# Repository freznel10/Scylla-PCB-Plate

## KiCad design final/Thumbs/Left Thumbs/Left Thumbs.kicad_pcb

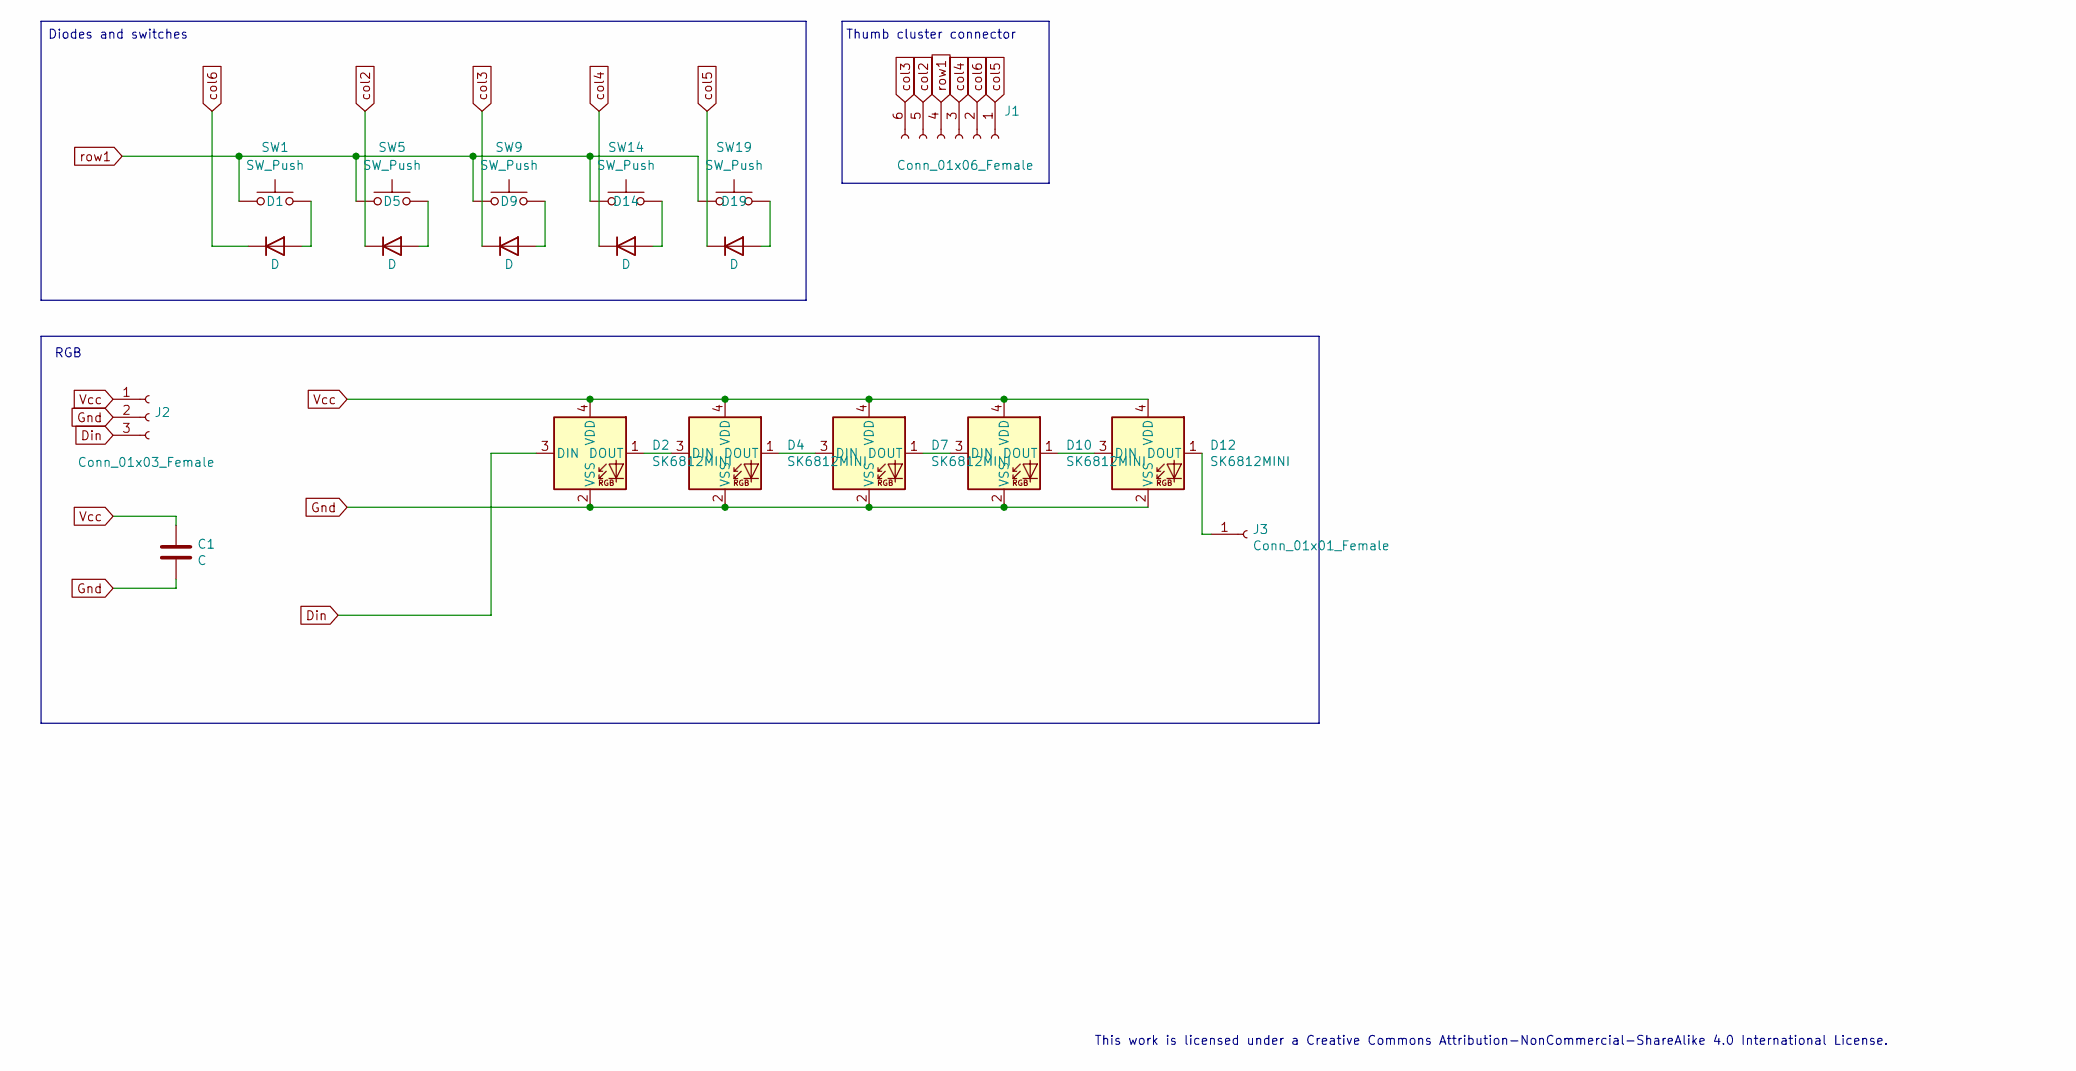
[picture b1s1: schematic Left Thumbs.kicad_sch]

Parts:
C1: C; C_0805_2012Metric_Pad1.18x1.45mm_HandSolder; LCSC C2798196
D1, D5, D9, D14, D19: D; Diode_TH_SOD123; LCSC C108804
D2, D4, D7, D10, D12: SK6812MINI; YS-SK6812MINI-E-bkb
J1: Conn_01x06_Female; PinHeader_1x06_P2.54mm_Vertical
J2: Conn_01x03_Female; PinHeader_1x03_P2.54mm_Vertical
J3: Conn_01x01_Female; PinHeader_1x01_P2.54mm_Vertical
SW1, SW5, SW9, SW14, SW19: SW_Push; SW_MX_KS_Choc-mod

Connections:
Din: D2.3 (DIN), J2.3
Gnd: C1.2, D2.2 (VSS), D4.2 (VSS), D7.2 (VSS), D10.2 (VSS), D12.2 (VSS), J2.2
unnamed: D1.2 (A), SW1.2
unnamed: D2.1 (DOUT), D4.3 (DIN)
unnamed: D4.1 (DOUT), D7.3 (DIN)
unnamed: D5.2 (A), SW5.2
unnamed: D9.2 (A), SW9.2
unnamed: D7.1 (DOUT), D10.3 (DIN)
unnamed: D10.1 (DOUT), D12.3 (DIN)
unnamed: D12.1 (DOUT), J3.1
unnamed: D14.2 (A), SW14.2
unnamed: D19.2 (A), SW19.2
Vcc: C1.1, D2.4 (VDD), D4.4 (VDD), D7.4 (VDD), D10.4 (VDD), D12.4 (VDD), J2.1
col2: D5.1 (K), J1.5
col3: D9.1 (K), J1.6
col4: D14.1 (K), J1.3
col5: D19.1 (K), J1.1
col6: D1.1 (K), J1.2
row1: J1.4, SW1.1, SW5.1, SW9.1, SW14.1, SW19.1

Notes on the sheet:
Diodes and switches
RGB
Thumb cluster connector
This work is licensed under a Creative Commons Attribution-NonCommercial-ShareAlike 4.0 International License.

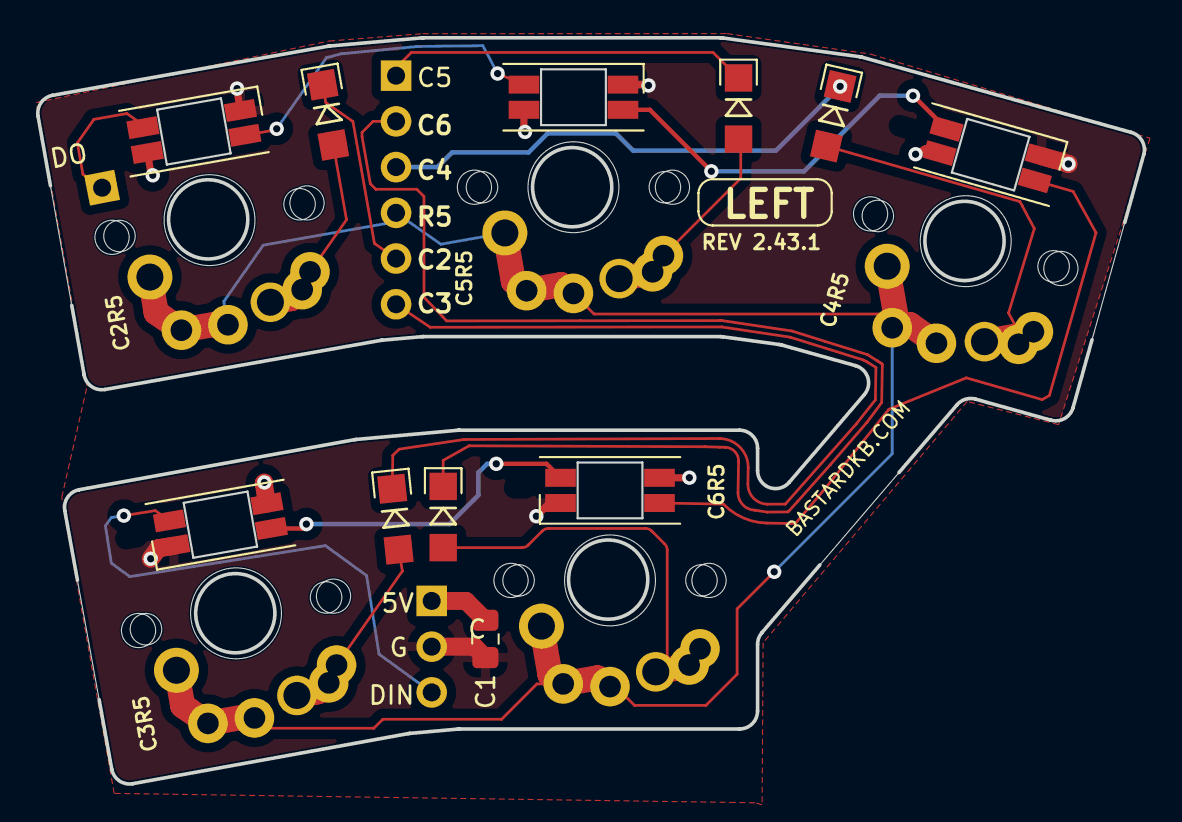
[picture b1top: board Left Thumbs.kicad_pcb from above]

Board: 4 copper layers, 61.5 x 41.5 mm, 19 parts (0 on the bottom side), 19 nets.

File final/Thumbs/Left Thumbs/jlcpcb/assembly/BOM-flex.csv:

Comment,Designator,Footprint,LCSC
D,"D1,D14,D19,D5,D9",Diode_TH_SOD123,C108804
C,C1,C_0805_2012Metric_Pad1.18x1.45mm_HandSolder,C2798196
Conn_01x03_Female,J2,PinHeader_1x03_P2.54mm_Vertical,
SK6812MINI,D4,YS-SK6812MINI-E-bkb,
SK6812MINI,D10,YS-SK6812MINI-E-bkb,
SW_Push,SW9,SW_MX_KS_Choc-mod,
SW_Push,SW19,SW_MX_KS_Choc-mod,
SW_Push,SW14,SW_MX_KS_Choc-mod,
SK6812MINI,D12,YS-SK6812MINI-E-bkb,
SK6812MINI,D2,YS-SK6812MINI-E-bkb,
Conn_01x06_Female,J1,PinHeader_1x06_P2.54mm_Vertical,
SW_Push,SW1,SW_MX_KS_Choc-mod,
SK6812MINI,D7,YS-SK6812MINI-E-bkb,
SW_Push,SW5,SW_MX_KS_Choc-mod,
Conn_01x01_Female,J3,PinHeader_1x01_P2.54mm_Vertical,

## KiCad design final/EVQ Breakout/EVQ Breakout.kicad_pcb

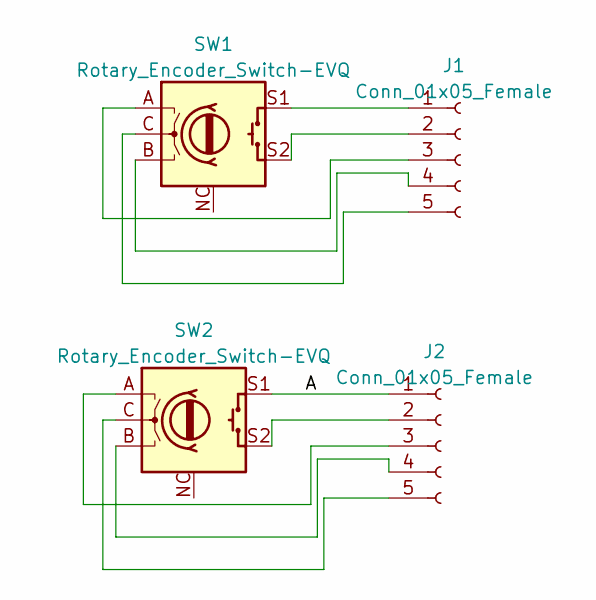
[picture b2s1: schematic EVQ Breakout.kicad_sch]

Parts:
J1, J2: Conn_01x05_Female; PinHeader_1x05_P2.00mm_Vertical
SW1, SW2: Rotary_Encoder_Switch-EVQ; EVQWGD001-sadek-no cutout

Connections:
unnamed: J1.1, SW1.S1
unnamed: J1.2, SW1.S2
unnamed: J1.3, SW1.A
unnamed: J1.4, SW1.B
unnamed: J1.5, SW1.C
unnamed: J2.1, SW2.S1
unnamed: J2.2, SW2.S2
unnamed: J2.3, SW2.A
unnamed: J2.4, SW2.B
unnamed: J2.5, SW2.C

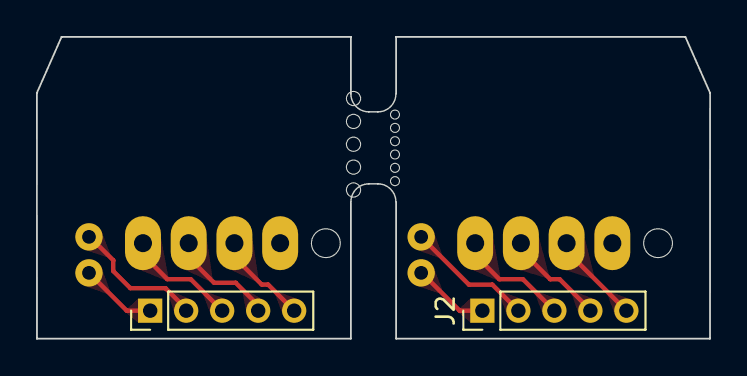
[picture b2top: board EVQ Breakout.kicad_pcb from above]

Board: 2 copper layers, 37.4 x 16.8 mm, 4 parts (0 on the bottom side), 10 nets.

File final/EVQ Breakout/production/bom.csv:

Designator,Footprint,Quantity,Value,LCSC Part #
"J1, J2",PinHeader_1x05_P2.00mm_Vertical,2,Conn_01x05_Female,
"SW1, SW2",EVQWGD001-sadek-no cutout,2,Rotary_Encoder_Switch-EVQ,

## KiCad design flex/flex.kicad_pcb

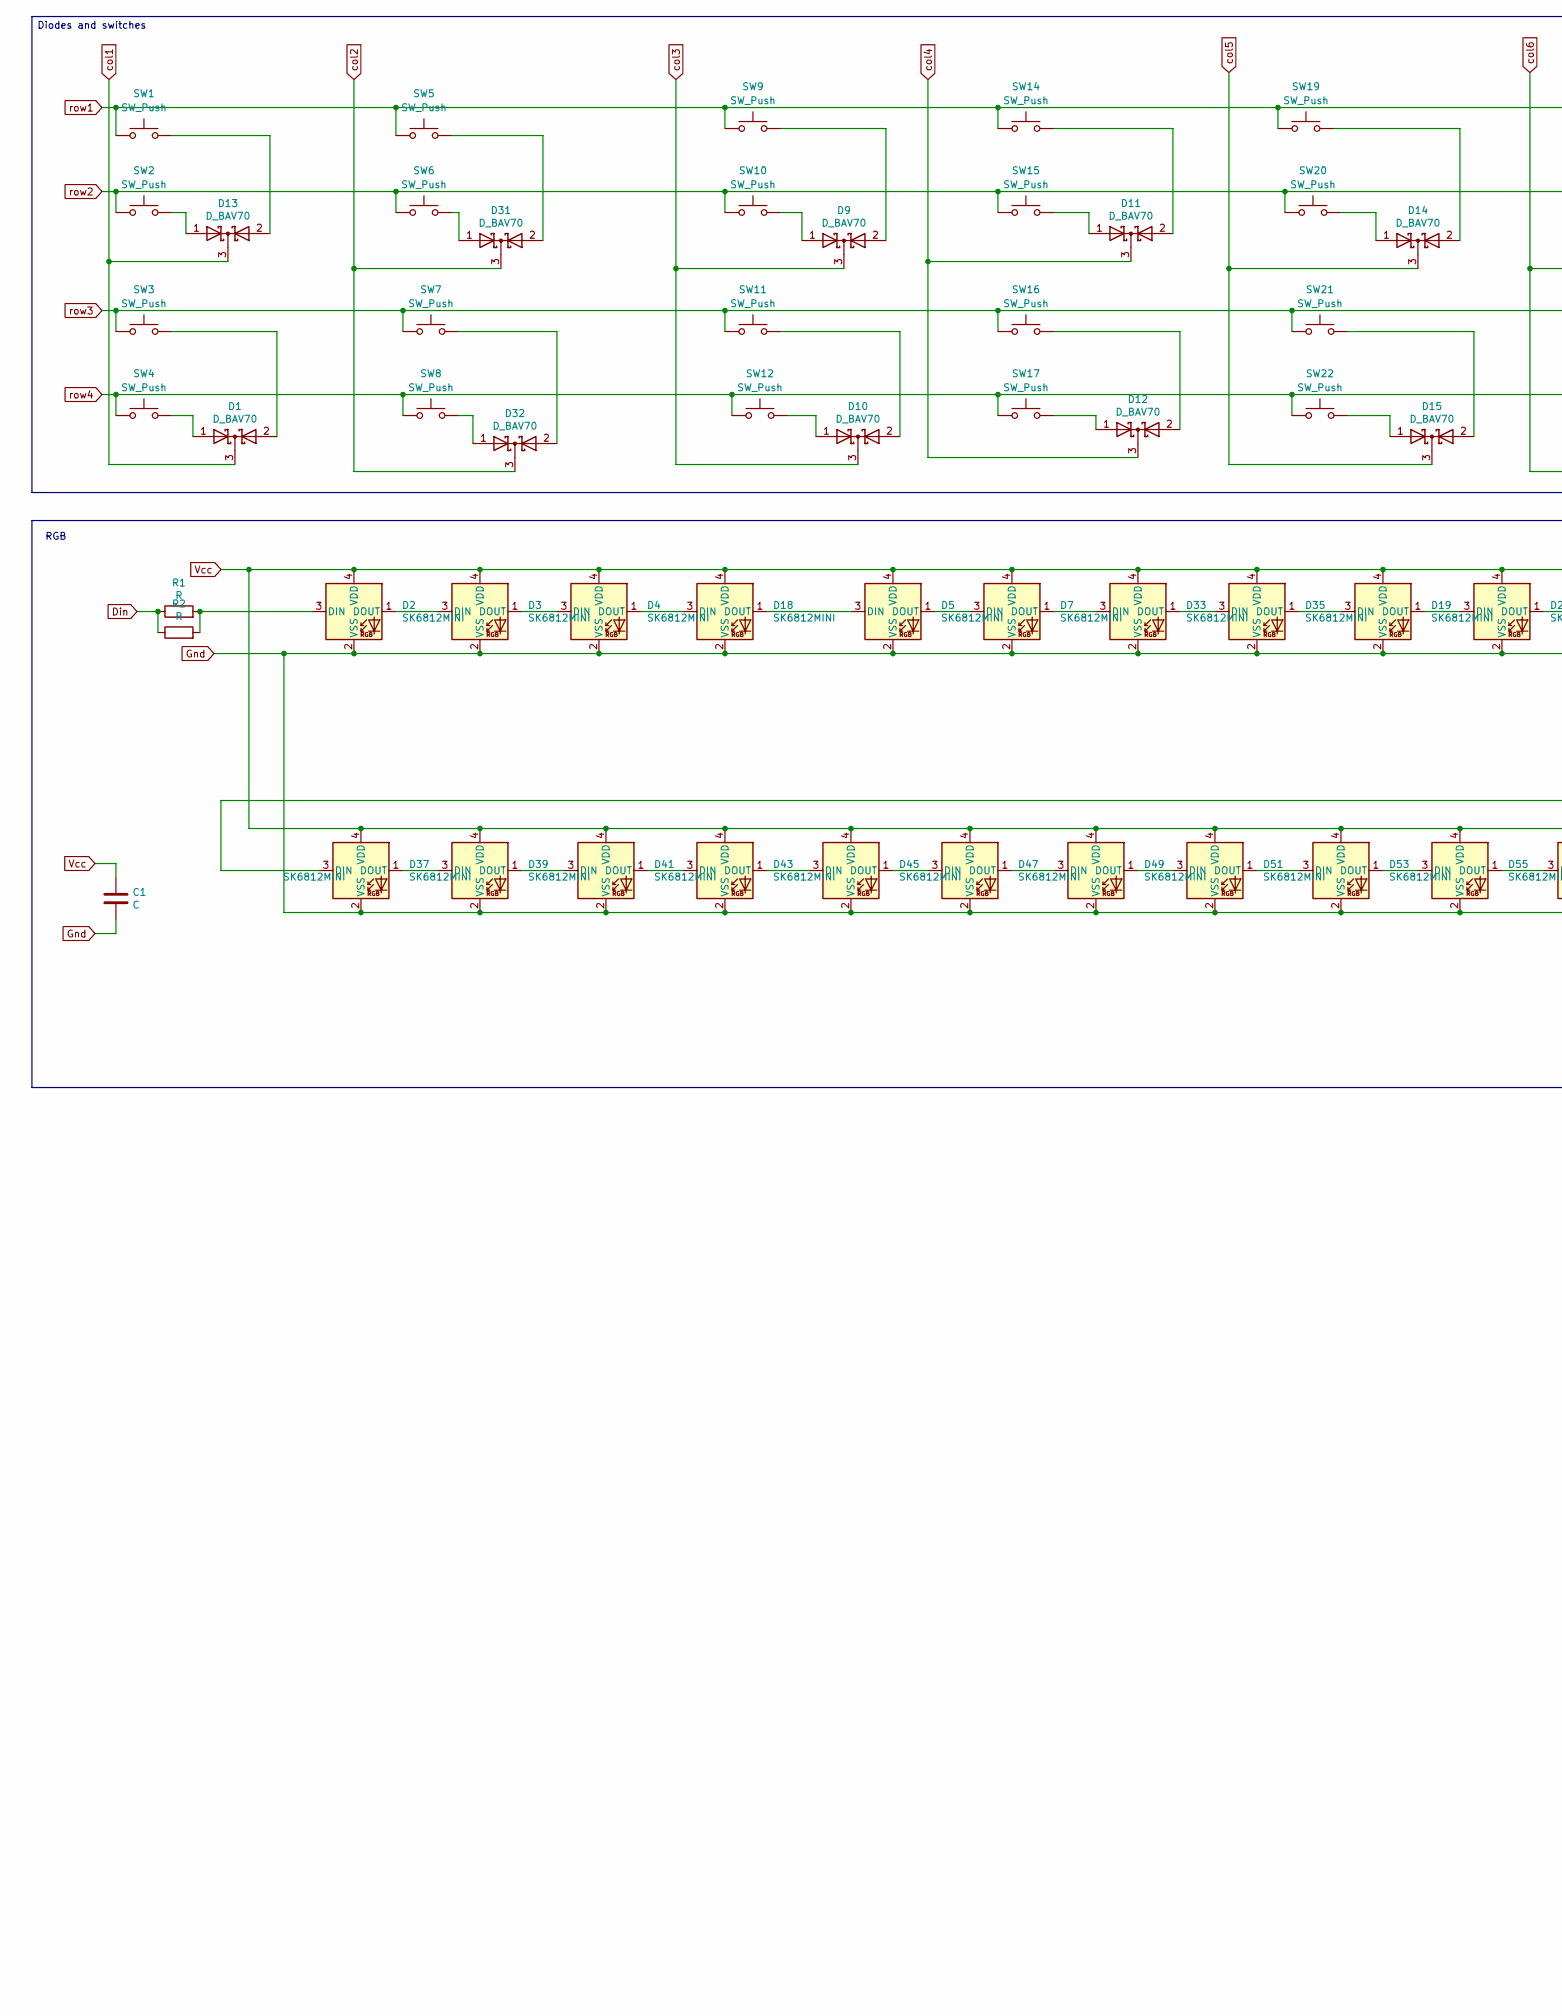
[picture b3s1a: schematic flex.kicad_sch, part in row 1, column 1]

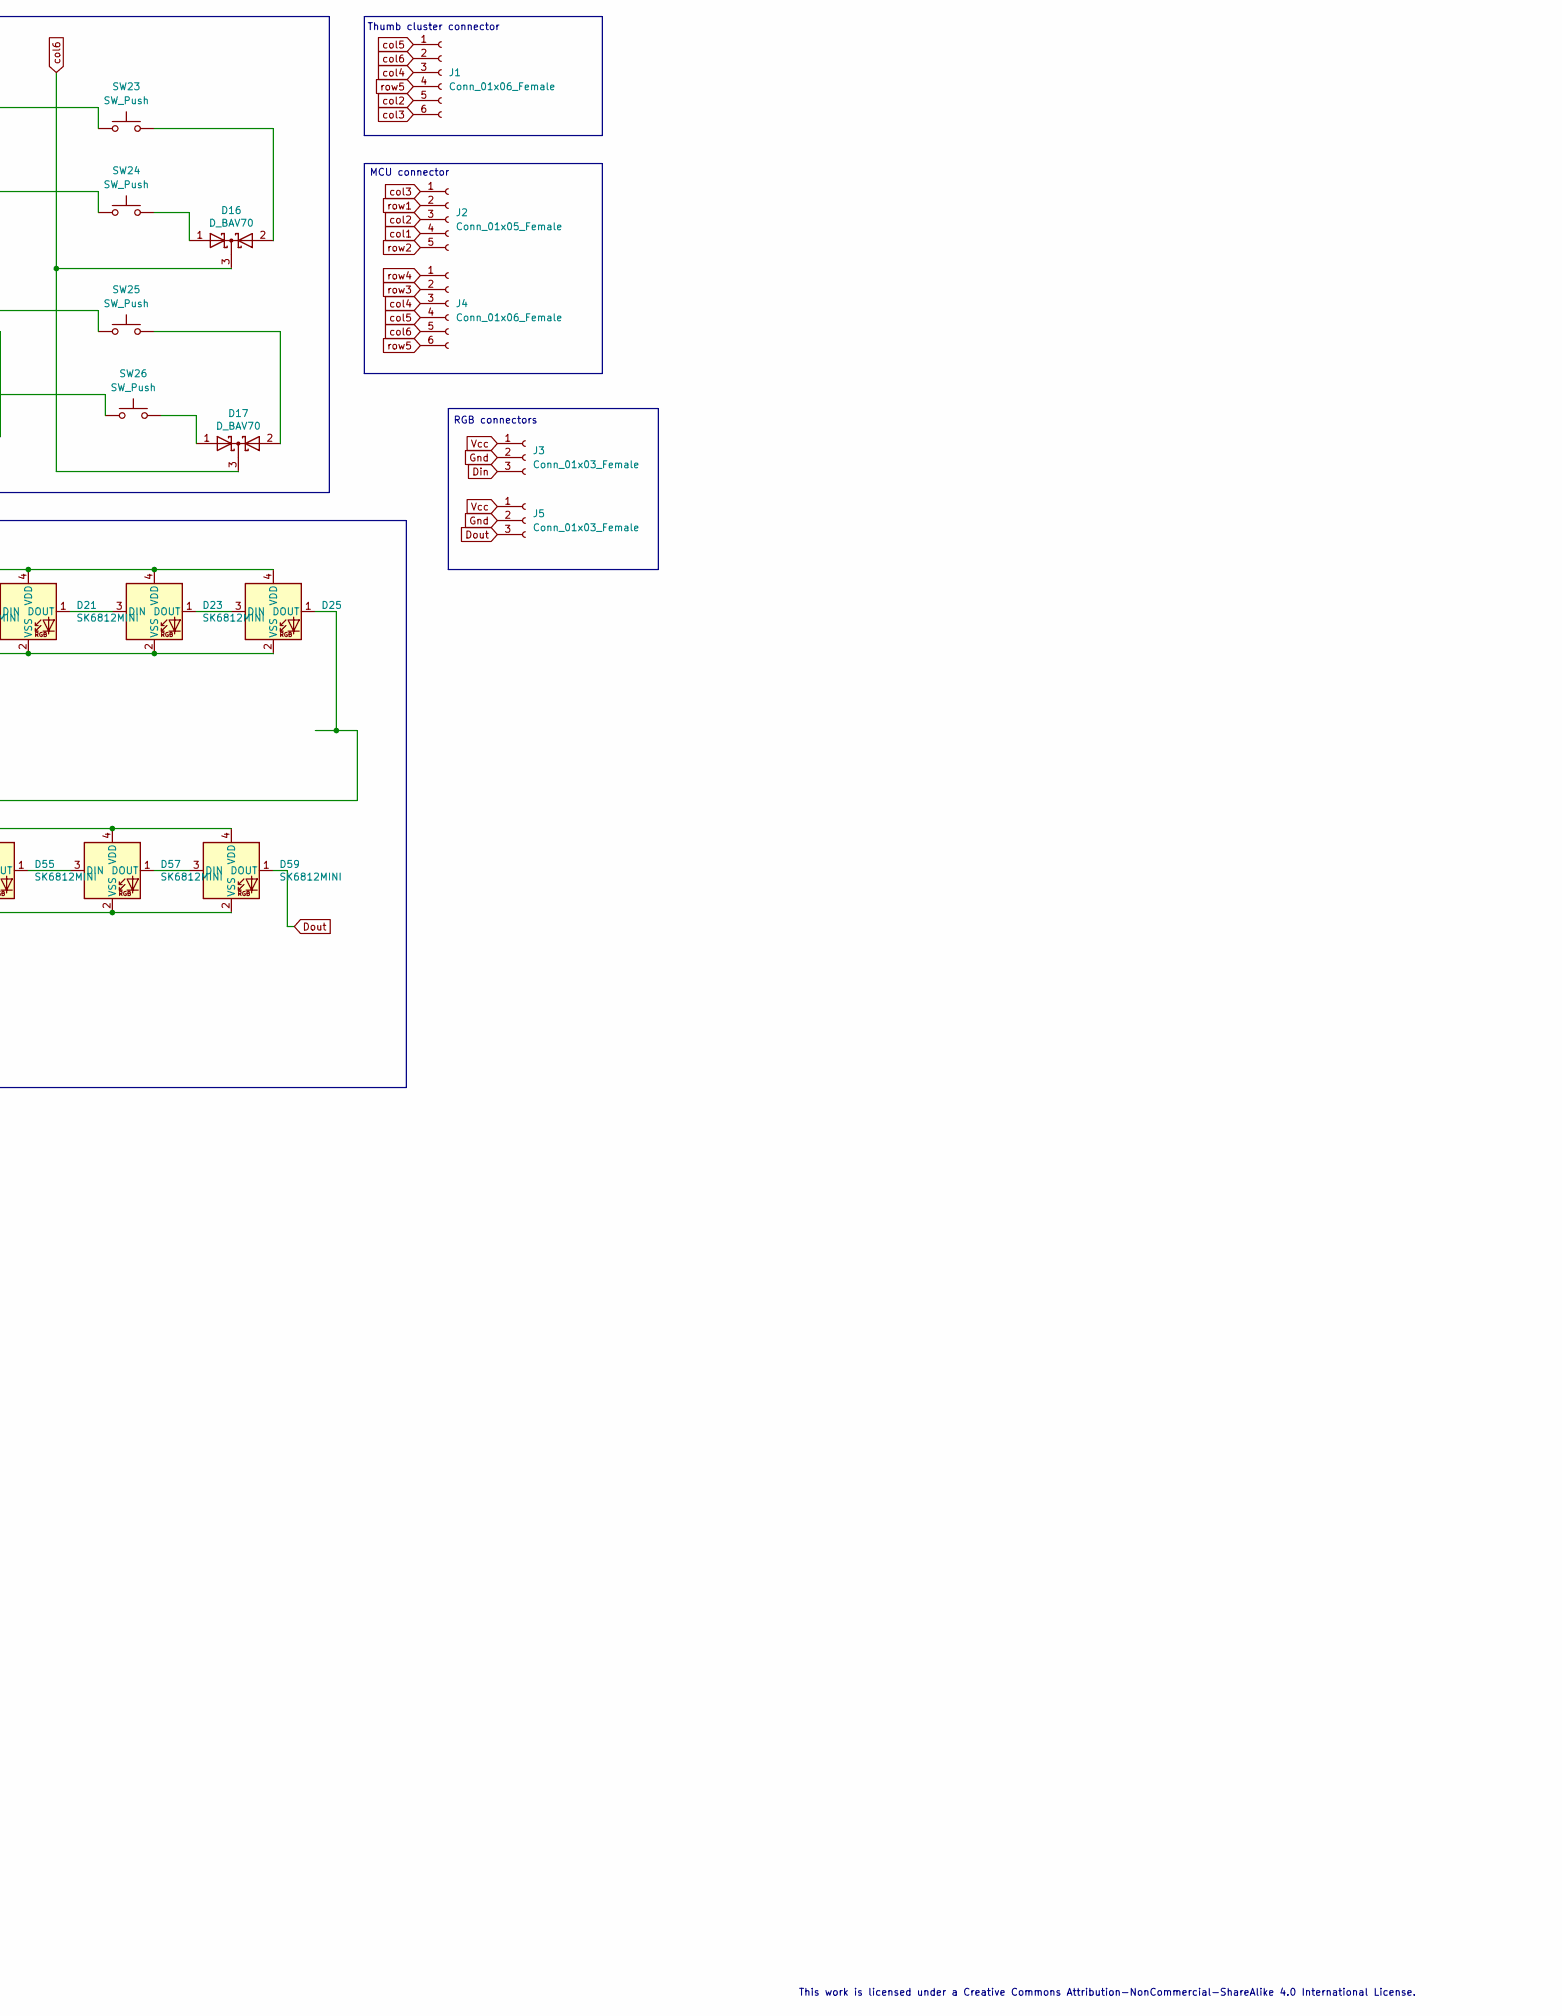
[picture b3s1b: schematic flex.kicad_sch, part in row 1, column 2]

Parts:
C1: C; C_1206_3216Metric_Pad1.42x1.75mm_HandSolder
D1, D9, D10, D11, D12, D13, D14, D15, D16, D17, D31, D32: D_BAV70; TSOT-23_HandSoldering; LCSC C68978
D2, D3, D4, D5, D7, D18, D19, D21, D23, D25, D33, D35, D37, D39, D41, D43, D45, D47, D49, D51, D53, D55, D57, D59: SK6812MINI; YS-SK6812MINI-E_REVERSE
J1, J4: Conn_01x06_Female; PinHeader_1x06_P2.54mm_Vertical
J2: Conn_01x05_Female; PinHeader_1x05_P2.54mm_Vertical
J3, J5: Conn_01x03_Female; PinHeader_1x03_P2.54mm_Vertical
R1, R2: R; R_1206_3216Metric_Pad1.42x1.75mm_HandSolder
SW1, SW2, SW3, SW4, SW5, SW6, SW7, SW8, SW9, SW10, SW11, SW12, SW14, SW15, SW16, SW17, SW19, SW20, SW21, SW22, SW23, SW24, SW25, SW26: SW_Push; MX100-ChocV1V2-flex

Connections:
Din: J3.3, R1.1, R2.1
Dout: D59.1 (DOUT), J5.3
Gnd: C1.2, D2.2 (VSS), D3.2 (VSS), D4.2 (VSS), D5.2 (VSS), D7.2 (VSS), D18.2 (VSS), D19.2 (VSS), D21.2 (VSS), D23.2 (VSS), D25.2 (VSS), D33.2 (VSS), D35.2 (VSS), D37.2 (VSS), D39.2 (VSS), D41.2 (VSS), D43.2 (VSS), D45.2 (VSS), D47.2 (VSS), D49.2 (VSS), D51.2 (VSS), D53.2 (VSS), D55.2 (VSS), D57.2 (VSS), D59.2 (VSS), J3.2, J5.2
unnamed: D1.2 (A), SW3.2
unnamed: D1.1 (A), SW4.2
unnamed: D2.3 (DIN), R1.2, R2.2
unnamed: D2.1 (DOUT), D3.3 (DIN)
unnamed: D3.1 (DOUT), D4.3 (DIN)
unnamed: D5.1 (DOUT), D7.3 (DIN)
unnamed: D9.2 (A), SW9.2
unnamed: D9.1 (A), SW10.2
unnamed: D10.2 (A), SW11.2
unnamed: D10.1 (A), SW12.2
unnamed: D11.2 (A), SW14.2
unnamed: D11.1 (A), SW15.2
unnamed: D12.2 (A), SW16.2
unnamed: D12.1 (A), SW17.2
unnamed: D13.1 (A), SW2.2
unnamed: D13.2 (A), SW1.2
unnamed: D14.2 (A), SW19.2
unnamed: D14.1 (A), SW20.2
unnamed: D15.2 (A), SW21.2
unnamed: D15.1 (A), SW22.2
unnamed: D16.2 (A), SW23.2
unnamed: D16.1 (A), SW24.2
unnamed: D17.2 (A), SW25.2
unnamed: D17.1 (A), SW26.2
unnamed: D4.1 (DOUT), D18.3 (DIN)
unnamed: D5.3 (DIN), D18.1 (DOUT)
unnamed: D19.3 (DIN), D35.1 (DOUT)
unnamed: D19.1 (DOUT), D21.3 (DIN)
unnamed: D21.1 (DOUT), D23.3 (DIN)
unnamed: D23.1 (DOUT), D25.3 (DIN)
unnamed: D25.1 (DOUT), D37.3 (DIN)
unnamed: D31.2 (A), SW5.2
unnamed: D31.1 (A), SW6.2
unnamed: D32.2 (A), SW7.2
unnamed: D32.1 (A), SW8.2
unnamed: D7.1 (DOUT), D33.3 (DIN)
unnamed: D33.1 (DOUT), D35.3 (DIN)
unnamed: D37.1 (DOUT), D39.3 (DIN)
unnamed: D39.1 (DOUT), D41.3 (DIN)
unnamed: D41.1 (DOUT), D43.3 (DIN)
unnamed: D43.1 (DOUT), D45.3 (DIN)
unnamed: D45.1 (DOUT), D47.3 (DIN)
unnamed: D47.1 (DOUT), D49.3 (DIN)
unnamed: D49.1 (DOUT), D51.3 (DIN)
unnamed: D51.1 (DOUT), D53.3 (DIN)
unnamed: D53.1 (DOUT), D55.3 (DIN)
unnamed: D55.1 (DOUT), D57.3 (DIN)
unnamed: D57.1 (DOUT), D59.3 (DIN)
Vcc: C1.1, D2.4 (VDD), D3.4 (VDD), D4.4 (VDD), D5.4 (VDD), D7.4 (VDD), D18.4 (VDD), D19.4 (VDD), D21.4 (VDD), D23.4 (VDD), D25.4 (VDD), D33.4 (VDD), D35.4 (VDD), D37.4 (VDD), D39.4 (VDD), D41.4 (VDD), D43.4 (VDD), D45.4 (VDD), D47.4 (VDD), D49.4 (VDD), D51.4 (VDD), D53.4 (VDD), D55.4 (VDD), D57.4 (VDD), D59.4 (VDD), J3.1, J5.1
col1: D1.3 (K), D13.3 (K), J2.4
col2: D31.3 (K), D32.3 (K), J1.5, J2.3
col3: D9.3 (K), D10.3 (K), J1.6, J2.1
col4: D11.3 (K), D12.3 (K), J1.3, J4.3
col5: D14.3 (K), D15.3 (K), J1.1, J4.4
col6: D16.3 (K), D17.3 (K), J1.2, J4.5
row1: J2.2, SW1.1, SW5.1, SW9.1, SW14.1, SW19.1, SW23.1
row2: J2.5, SW2.1, SW6.1, SW10.1, SW15.1, SW20.1, SW24.1
row3: J4.2, SW3.1, SW7.1, SW11.1, SW16.1, SW21.1, SW25.1
row4: J4.1, SW4.1, SW8.1, SW12.1, SW17.1, SW22.1, SW26.1
row5: J1.4, J4.6

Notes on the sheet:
Diodes and switches
RGB
MCU connector
Thumb cluster connector
This work is licensed under a Creative Commons Attribution-NonCommercial-ShareAlike 4.0 International License.
RGB connectors

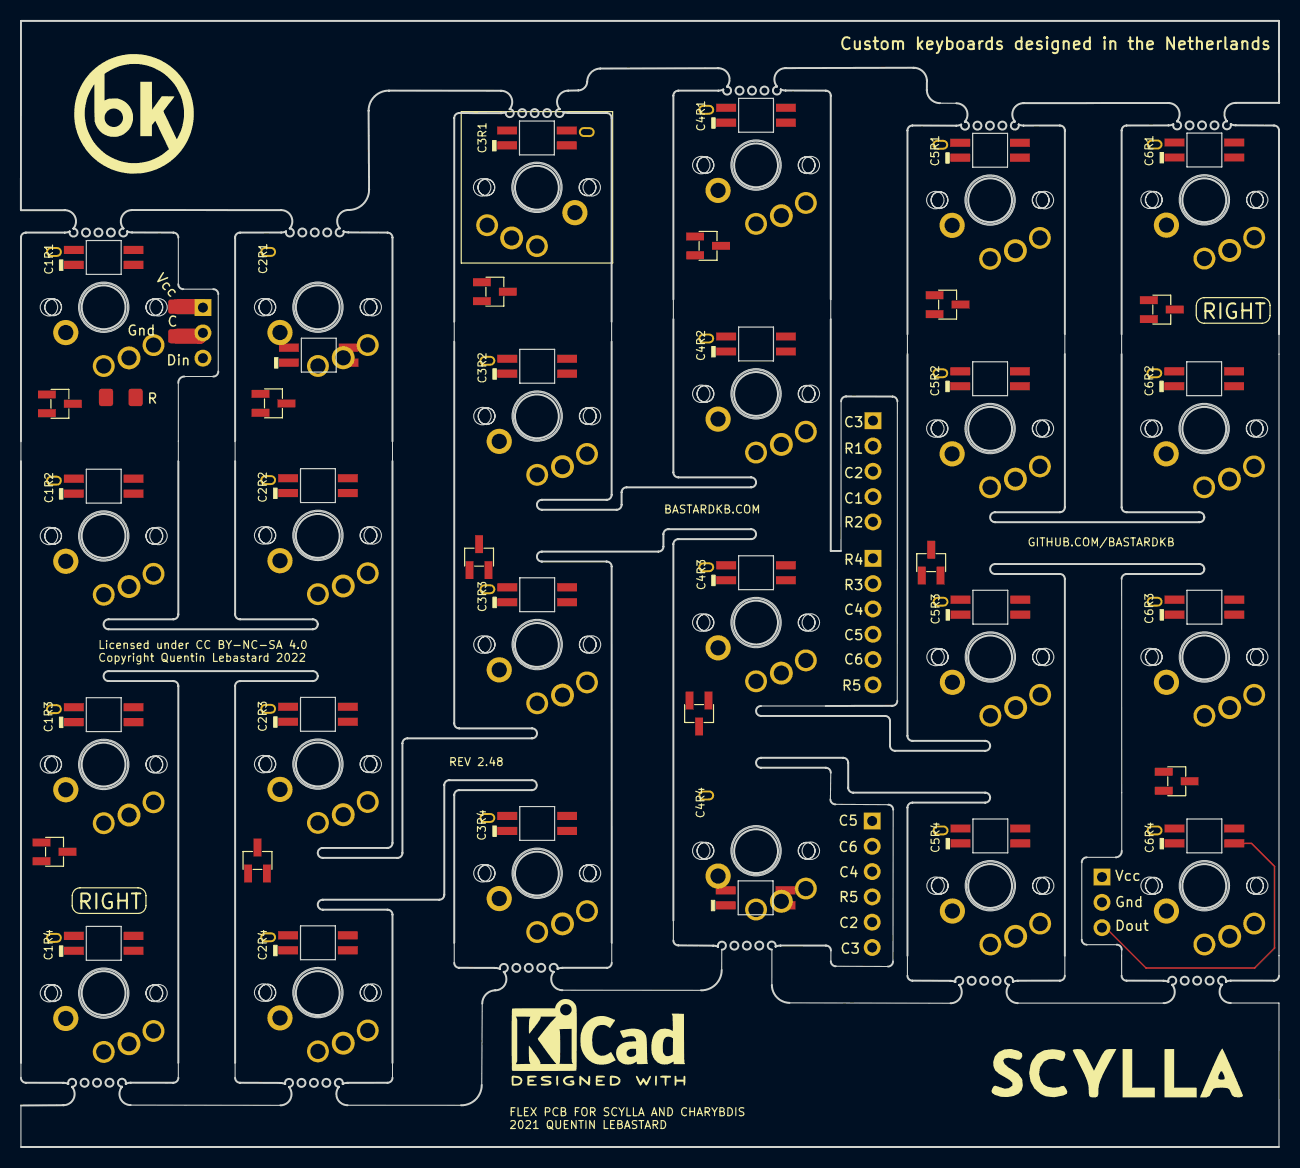
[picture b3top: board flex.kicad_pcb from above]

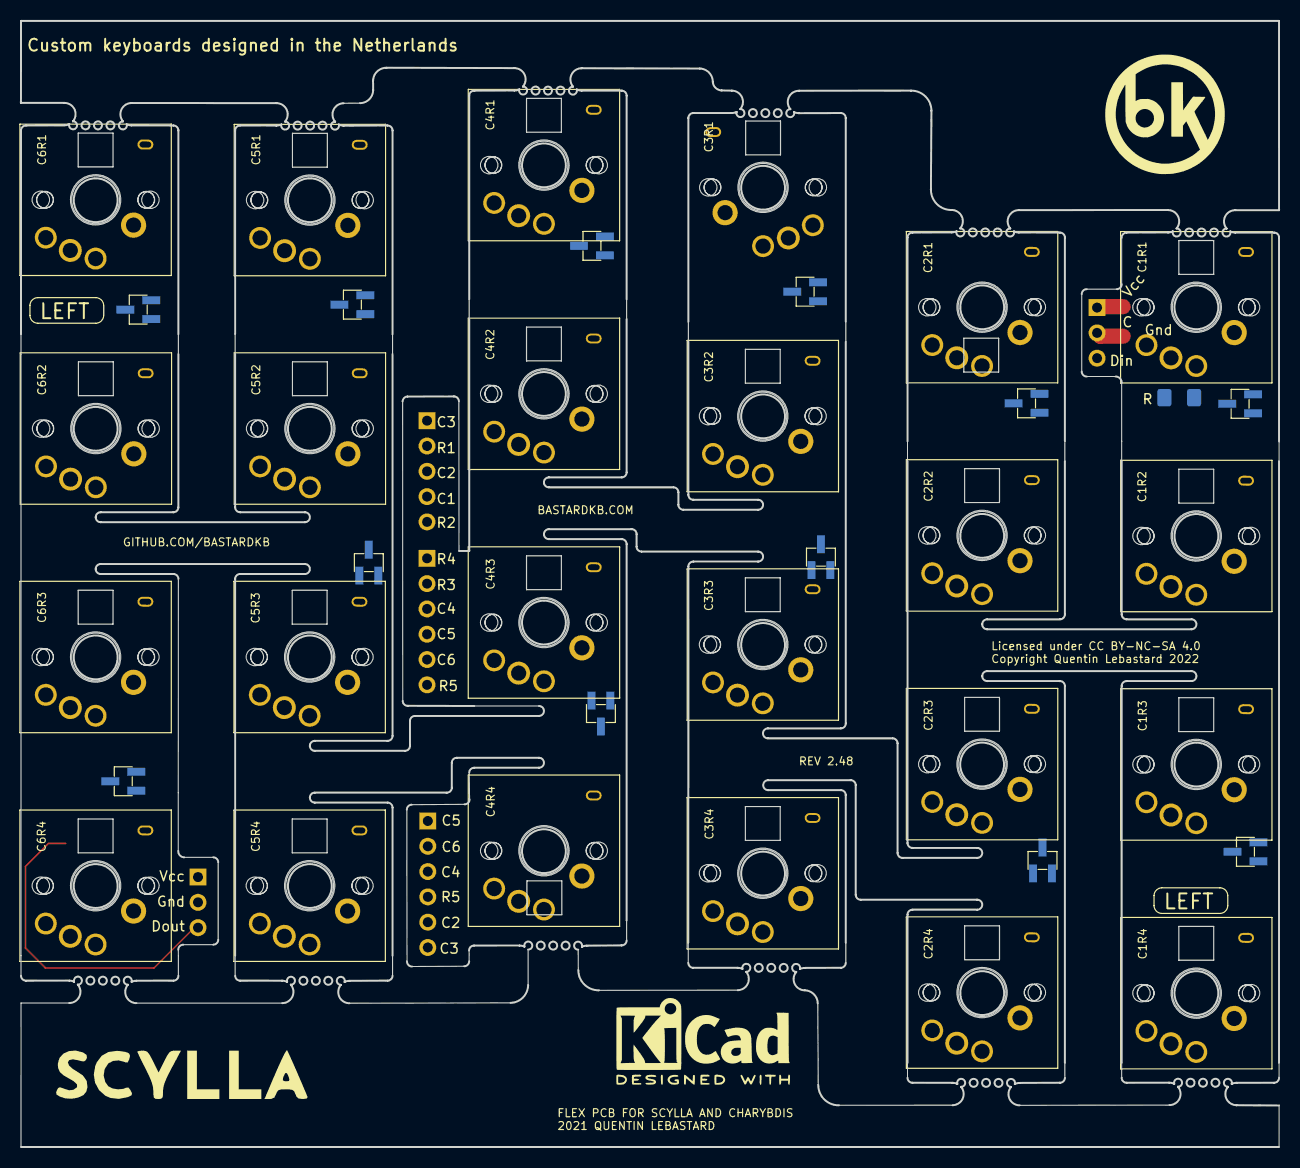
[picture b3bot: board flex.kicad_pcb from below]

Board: 2 copper layers, 126.3 x 113.0 mm, 68 parts (2 on the bottom side), 63 nets.

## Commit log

2022-12-07 MCU, flex plates
2022-12-07 MCU and Flex
2022-12-07 initial upload
2022-12-07 EVQ breakout
2022-12-07 thumbs
2022-12-07 updated the magnet mount for oled cover on the main case
    updated the magnet mount for oled on the main case
2022-12-09 v2 acrylics
2022-12-12 New V2 cases uploaded (Choc and MX)

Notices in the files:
final/Thumbs/Left Thumbs/Left Thumbs.kicad_sch:
CC BY-NC-SA 4.0
Copyright Quentin Lebastard 2022
flex/flex.kicad_pcb:
Licensed under CC BY-NC-SA 4.0
